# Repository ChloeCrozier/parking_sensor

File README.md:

## Embedded Systems Parking Sensor and Occupancy Detection Monitor
Embedded motion sensor that uses an MSB430 Texas Instruments microcontroller to transmit parking space occupancy information.
### Parkshark's Team Members:

- Chloe Crozier | [cscrozi@clemson.edu](mailto:cscrozi@clemson.edu)
- Eliza Sorber | [esorber@clemson.edu](mailto:esorber@clemson.edu)
- Charlie Medlock | [medloc5@clemson.edu](mailto:medloc5@clemson.edu)
- Harrison Langpaul | [hlangpa@clemson.edu](mailto:hlangpa@clemson.edu)

---

- Object Detection with Ultrasound Sensor:
  - The ultrasound sensor detects an object within half of a pre-set 'parking spot' distance.
  - Once the object has been detected for a given number of cycles, it is considered parked.
- LED Status Indication:
  - The LEDs toggle from blue (unoccupied) to red (occupied) to indicate the parking spot status.
- Microphone Polling for Object Departure Detection:
  - After an object is parked, microphone polling is turned on to detect low-frequency noises that suggest the object may be leaving the spot (e.g., engine rumble or footsteps).
- Polling Rate Adjustment with Yellow LED:
  - The ultrasound sensor's polling rate is increased when the yellow LED indicates noise above the set threshold.
- Reverting to Original Polling Rate:
  - When the ultrasound no longer detects an object, microphone polling is turned off, and the ultrasound polling rate is decreased back to the original slow cycle.
- System Controls:
  - There is a button to turn the system on/off.
  - Another button is used to turn debug mode on/off, indicated by LED indicators.
- Potentiometer Path Selection for Filtering:
  - A switch is used to select the potentiometer path when correcting envelope distortions in the microphone filtering.
- Radio Communication for Data Transmission:
  - Radio communication is utilized to transmit information about the status of a parking spot (empty or occupied) and the duration for which an object has been parked.

---

## UNIT TESTING:

### Ultrasound Sensor Testing:

1. Navigate to `ultrasound_testing --> ultrasound_unit_testing` and open the module in Energia (`ultrasound_unit_testing.ino`).
2. Set up a Launchpad with an ultrasound monitor (e.g., a breadboard).
3. Change the `DEBUG_MODE` macro at the top to `true`.
4. Upload the code to your Launchpad.
5. Open the serial monitor to view how many of the tests have passed. These tests validate a valid distance measured, valid measurement based on parking spot size, occupation status, and parking status.

### Radio Testing:

1. For a non-modular version, use the TX/RX examples in the Buffet repository.
2. For a modular design, navigate to `radio_testing --> radio_unit_testing` and open the module in Energia (`radio_unit_testing.ino`).
3. Set up two Launchpads with a CC1101 radio.
4. Set up a TX Launchpad and upload the code with `RECEIVING` and `DEBUG_MODE` set to `false`.
5. Set up a RX Launchpad and upload the code with `RECEIVING` and `DEBUG_MODE` set to `true`.
6. Plug in the transmitting Launchpad after the code starts running on the receiving Launchpad. Verify that the correct number of packets were received, and that the value of the last packet received and the sum of all packets received are accurate.

### Microphone Testing:

1. Navigate to `microphone_unit_testing` and open the module in Energia (`microphone_unit_testing.ino`).
2. Set up a Launchpad with a microphone and upload the code.
3. Set `DEBUG_MODE` to `true` and run the code. The serial monitor will print which tests have passed.
4. For the tests verifying that the LED does/doesn't turn on, manually observe the LED behavior. Ensure that it blinks exactly as expected for each test case. These tests measure the bounds of the microphone thresholds and detect noise above a specified level.

---

## INTEGRATION TESTING:

### Radio Ultrasound Testing:

1. Navigate to `integration_testing --> ultrasound_radio_testing` and open the module in Energia (`ultrasound_radio_testing.ino`).
2. Set up a TX Launchpad with a radio and an ultrasound and upload the code with `RECEIVING` and `DEBUG_MODE` set to `false`.
3. Set up a RX Launchpad with a radio and upload the code with `RECEIVING` and `DEBUG_MODE` set to `true`.
4. Plug in the transmitting Launchpad after the code starts running on the receiving Launchpad. Verify that the correct number of packets are received and that the final parking state is accurately transmitted and calculated from the valid transmitted distances.

### Radio Microphone Ultrasound Testing:

1. Navigate to `integration_testing --> mic_radio_ultrasound_testing` and open the module in Energia (`mic_radio_ultrasound_testing.ino`).
2. Set up a TX Launchpad with a radio and an ultrasound and upload the code with `RECEIVING` and `DEBUG_MODE` set to `false`.
3. Set up a RX Launchpad with a radio and upload the code with `RECEIVING` and `DEBUG_MODE` set to `true`.
4. Plug in the transmitting Launchpad after the code starts running on the receiving Launchpad. Verify that the correct number of packets are received and that the final parking state is accurately transmitted and calculated from the valid transmitted distances. Ensure that the microphone responds to the specified intervals.

---

## FINAL DEMO TESTING:

### Parking Sensor Demo:

1. Navigate to the `parking_sensor_demo` folder and open the module in Energia (`parking_sensor_demo.ino`).

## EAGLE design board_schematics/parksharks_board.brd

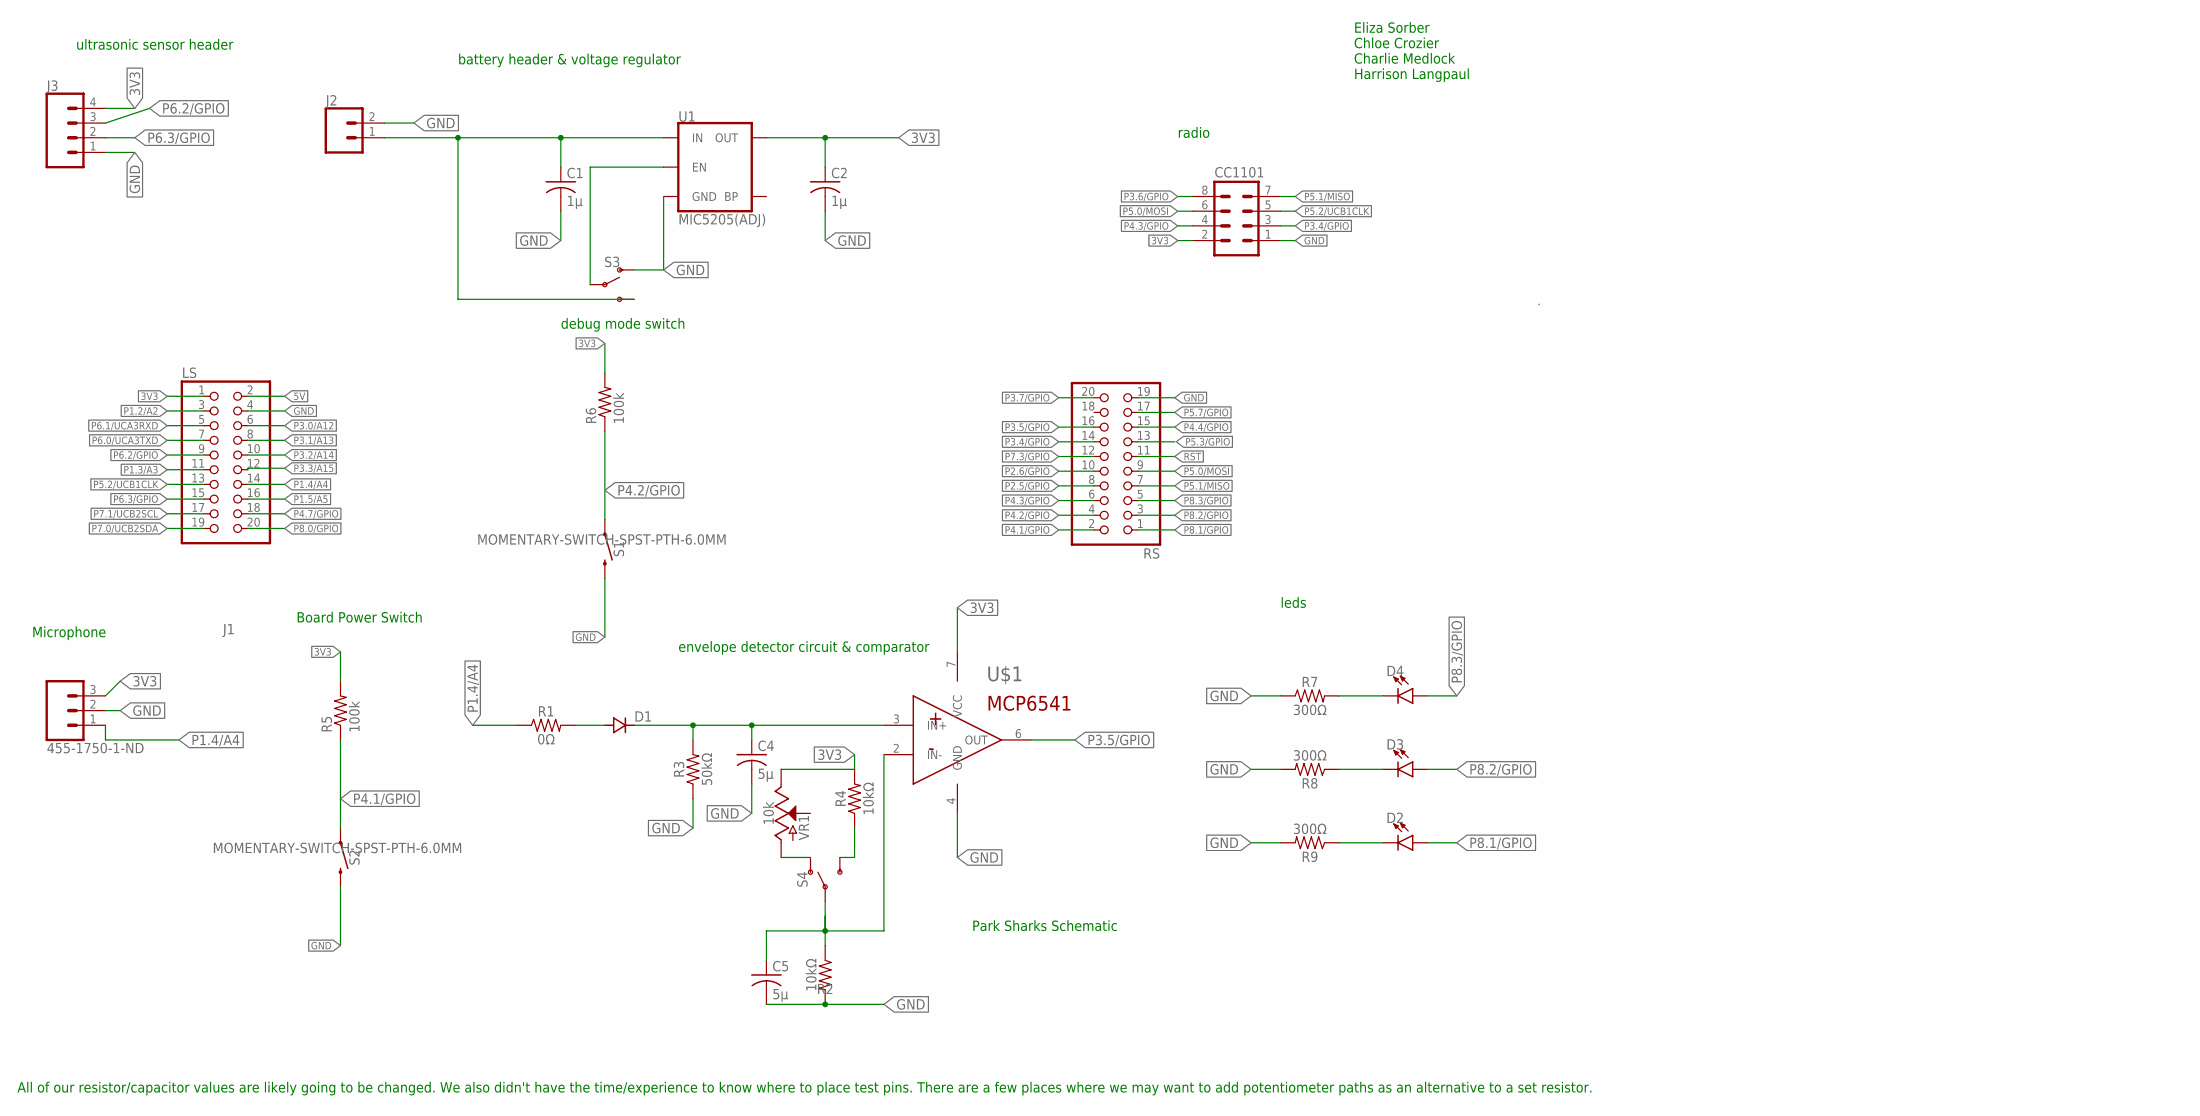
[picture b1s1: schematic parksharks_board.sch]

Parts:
C1, C2: 1µ; C0805
C4, C5: 5µ; C0805
CC1101: MA04-2
D1: DSOD323; SOD323
D2, D3, D4: LED5MM; LED_5MM
J1: 455-1750-1-ND; 1X03
J2: CONN_02; 1X02
J3: CONN_04JST-PTH; JST-4-PTH
LS: PINHD-2X10; 2X10
R1: 0Ω; 0805
R2, R4: 10kΩ; 0805
R3: 50kΩ; 0805
R5, R6: 100k; R0805
R7, R8, R9: 300Ω; 0805
RS: PINHD-2X10; 2X10
S1, S2: MOMENTARY-SWITCH-SPST-PTH-6.0MM; TACTILE_SWITCH_PTH_6.0MM
S3, S4: SWITCH-SPDT-PTH-11.6X4.0MM; SWITCH_SPDT_PTH_11.6X4.0MM
U1: MIC5205(ADJ); SOT23-5
U$1: MCP654!; DIP08
VR1: 10k; POT-PTH-ALPS

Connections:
3V3: C2.1, CC1101.2, J1.3, J3.4, LS.1, R4.2, R5.2, R6.2, U1.5 (OUT), U$1.7 (VCC), VR1.P$1 (E)
5V: LS.2
GND: C1.2, C2.2, C4.2, C5.2, CC1101.1, J1.2, J2.2, J3.1, LS.4, R2.2, R3.1, R7.1, R8.2, R9.2, RS.19, S1.3 (2), S2.3 (2), S3.1 (O), U1.2 (GND), U$1.4 (GND)
unnamed: D1.2 (A), R1.2
unnamed: C4.1, D1.1 (C), R3.2, U$1.3 (IN+)
unnamed: C5.1, R2.1, S4.2, U$1.2 (IN-)
unnamed: S3.2, U1.3 (EN)
unnamed: S4.1 (O), VR1.P$3 (A)
unnamed: R4.1, S4.3 (S)
unnamed: C1.1, J2.1, S3.3 (S), U1.1 (IN)
unnamed: D4.K (C), R7.2
unnamed: D3.K (C), R8.1
unnamed: D2.K (C), R9.1
P1.2/A2: LS.3
P1.3/A3: LS.11
P1.4/A4: J1.1, LS.14, R1.1
P1.5/A5: LS.16
P2.5/GPIO: RS.8
P2.6/GPIO: RS.10
P3.0/A12: LS.6
P3.1/A13: LS.8
P3.2/A14: LS.10
P3.3/A15: LS.12
P3.4/GPIO: CC1101.3, RS.14
P3.5/GPIO: RS.16, U$1.6 (OUT)
P3.6/GPIO: CC1101.8
P3.7/GPIO: RS.20
P4.1/GPIO: R5.1, RS.2, S2.1
P4.2/GPIO: R6.1, RS.4, S1.1
P4.3/GPIO: CC1101.4, RS.6
P4.4/GPIO: RS.15
P4.7/GPIO: LS.18
P5.0/MOSI: CC1101.6, RS.9
P5.1/MISO: CC1101.7, RS.7
P5.2/UCB1CLK: CC1101.5, LS.13
P5.3/GPIO: RS.13
P5.7/GPIO: RS.17
P6.0/UCA3TXD: LS.7
P6.1/UCA3RXD: LS.5
P6.2/GPIO: J3.3, LS.9
P6.3/GPIO: J3.2, LS.15
P7.0/UCB2SDA: LS.19
P7.1/UCB2SCL: LS.17
P7.3/GPIO: RS.12
P8.0/GPIO: LS.20
P8.1/GPIO: D2.A, RS.1
P8.2/GPIO: D3.A, RS.3
P8.3/GPIO: D4.A, RS.5
RST: RS.11

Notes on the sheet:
Board Power Switch
Microphone
debug mode switch
battery header & voltage regulator
ultrasonic sensor header
radio
envelope detector circuit & comparator
leds
All of our resistor/capacitor values are likely going to be changed. We also didn't have the time/experience to know where to place test pins. There are a few places where we may want to add potentiometer paths as an alternative to a set resistor.
Eliza Sorber Chloe Crozier Charlie Medlock Harrison Langpaul
Park Sharks Schematic

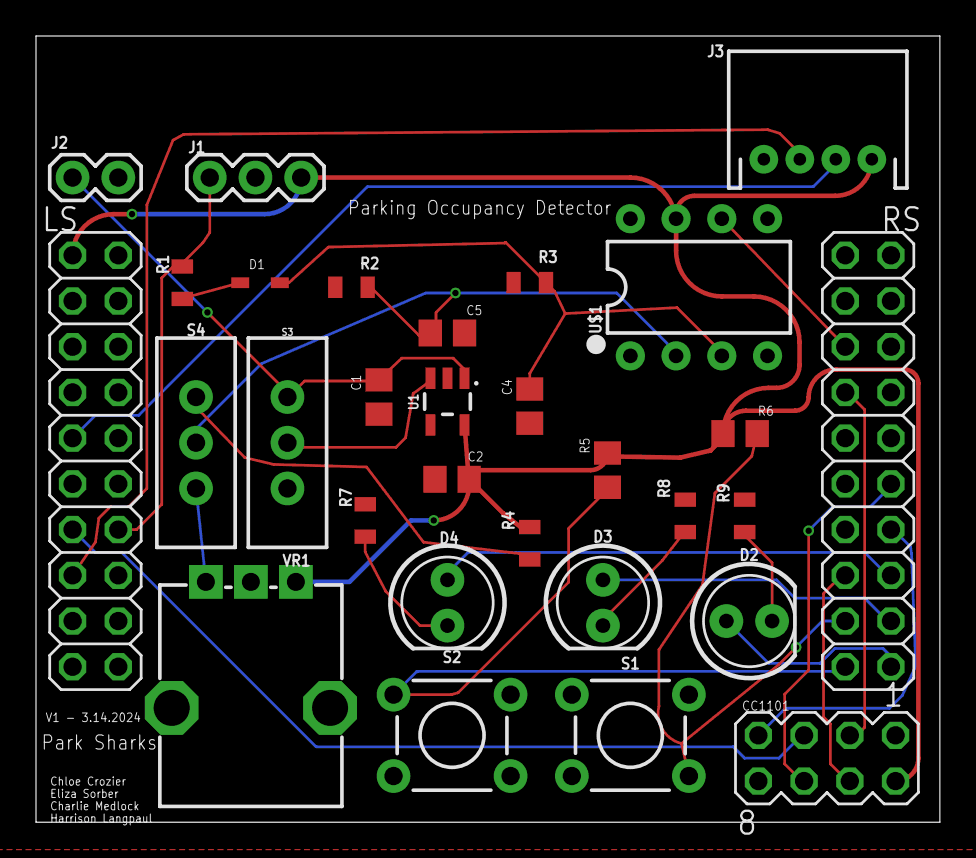
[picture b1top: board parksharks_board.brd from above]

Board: 2 copper layers, 50.2 x 43.7 mm, 30 parts (0 on the bottom side), 26 nets.

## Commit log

2024-04-27 adding full integration and mic testing modules
2024-04-27 updated readme and removed hidden files
2024-04-27 cleaned up folders
2024-04-27 added board and schematic files
2024-05-02 final demo code
2024-05-07 most updated demo code
2024-05-09 added board picture

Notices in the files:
parts and their libraries:
SparkFun-LED: Licensing: Creative Commons ShareAlike 4.0 International - https://creativecommons.org/licenses/by-sa/4.0
